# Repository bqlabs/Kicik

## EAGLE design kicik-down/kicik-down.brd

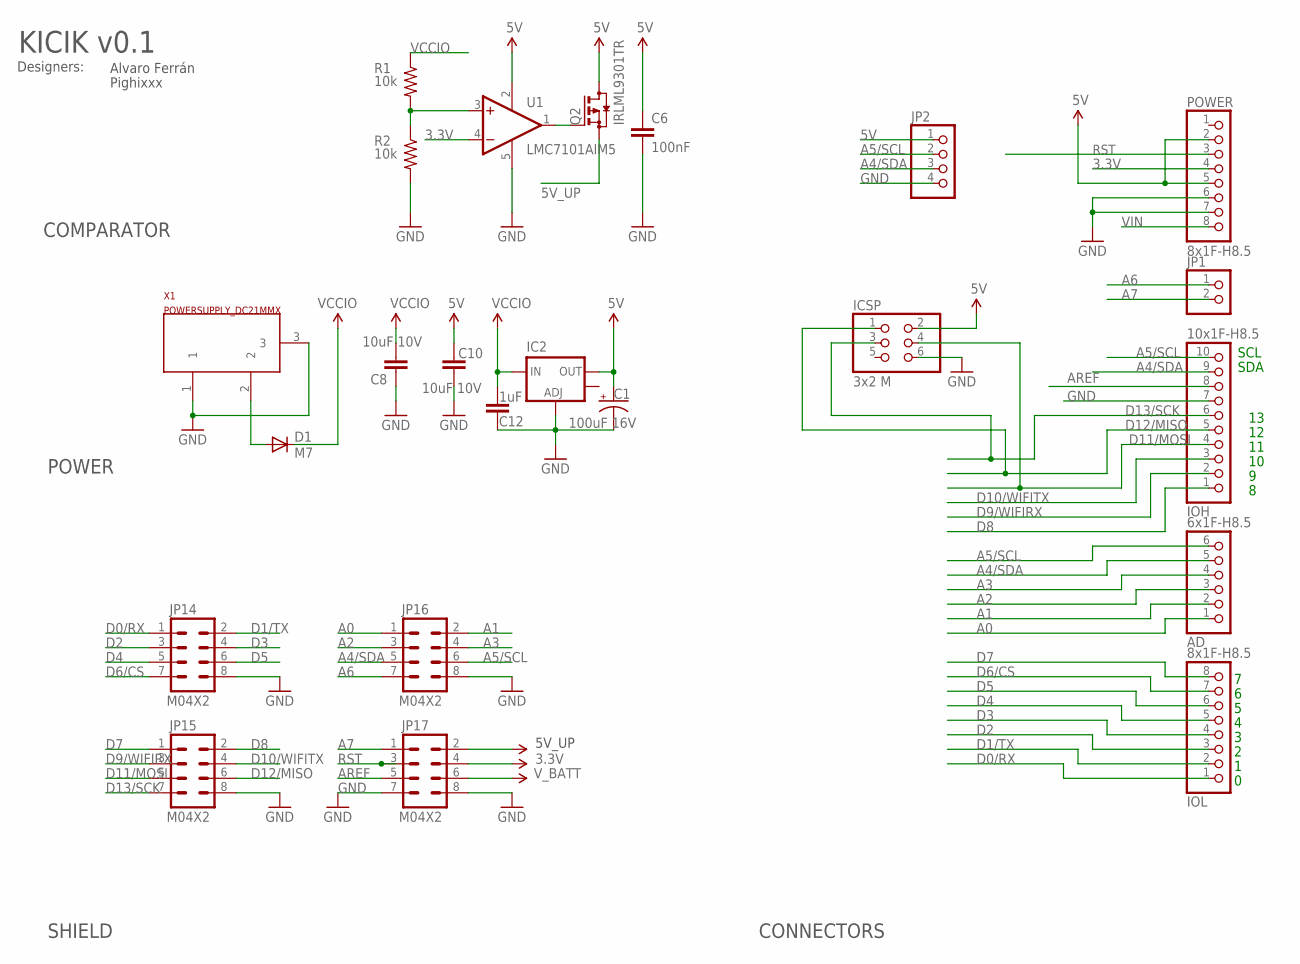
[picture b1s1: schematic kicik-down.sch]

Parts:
AD: 6x1F-H8.5; 1X06
C1: 100uF 16V; PANASONIC_C
C6: 100nF; 0402-CAP
C8, C10: 10uF 10V; 0402-CAP
C12: 1uF; 0402-CAP
D1: M7; SMB
IC2: V_REG_LM1117SOT223; SOT223
ICSP: 3x2 M; 2X03
IOH: 10x1F-H8.5; 1X10
IOL: 8x1F-H8.5; 1X08
JP1: PINHD-1X2; 1X02
JP2: PINHD-1X4; 1X04
JP14, JP15, JP16, JP17: M04X2; 2X4
POWER: 8x1F-H8.5; 1X08
Q2: IRLML9301TR; SOT23
R1, R2: 10k; 0402-RES
U1: LMC7101AIM5; SOT23-5
X1: POWERSUPPLY_DC21MMX; POWERSUPPLY_DC-21MM

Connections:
3.3V: JP17.4, POWER.4, U1.4 (-IN)
5V: C1.+, C6.1, C10.2, IC2.2 (OUT), ICSP.2, JP2.1, POWER.2, POWER.5, Q2.3 (D), U1.2 (V+)
5V_UP: JP17.2, Q2.2 (S)
A0: AD.1, JP16.1
A1: AD.2, JP16.2
A2: AD.3, JP16.3
A3: AD.4, JP16.4
A4/SDA: AD.5, IOH.9, JP2.3, JP16.5
A5/SCL: AD.6, IOH.10, JP2.2, JP16.6
A6: JP1.1, JP16.7
A7: JP1.2, JP17.1
AREF: IOH.8, JP17.5
D0/RX: IOL.1, JP14.1
D1/TX: IOL.2, JP14.2
D2: IOL.3, JP14.3
D3: IOL.4, JP14.4
D4: IOL.5, JP14.5
D5: IOL.6, JP14.6
D6/CS: IOL.7, JP14.7
D7: IOL.8, JP15.1
D8: IOH.1, JP15.2
D9/WIFIRX: IOH.2, JP15.3
D10/WIFITX: IOH.3, JP15.4
D11/MOSI: ICSP.4, IOH.4, JP15.5
D12/MISO: ICSP.1, IOH.5, JP15.6
D13/SCK: ICSP.3, IOH.6, JP15.7
GND: C1.-, C6.2, C8.1, C10.1, C12.1, IC2.1 (ADJ), ICSP.6, IOH.7, JP2.4, JP14.8, JP15.8, JP16.8, JP17.7, JP17.8, POWER.6, POWER.7, R2.2, U1.5 (V-), X1.1, X1.3
unnamed: D1.A, X1.2
unnamed: Q2.1 (G), U1.1 (OUT)
unnamed: R1.2, R2.1, U1.3 (+IN)
RST: JP17.3, POWER.3
VCCIO: C8.2, C12.2, D1.C, IC2.3 (IN), R1.1
VIN: POWER.8
V_BATT: JP17.6

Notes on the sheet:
SDA
SCL
KICIK v0.1
Designers:
Alvaro Ferrán
Pighixxx
POWER
SHIELD
CONNECTORS
COMPARATOR
5V_UP

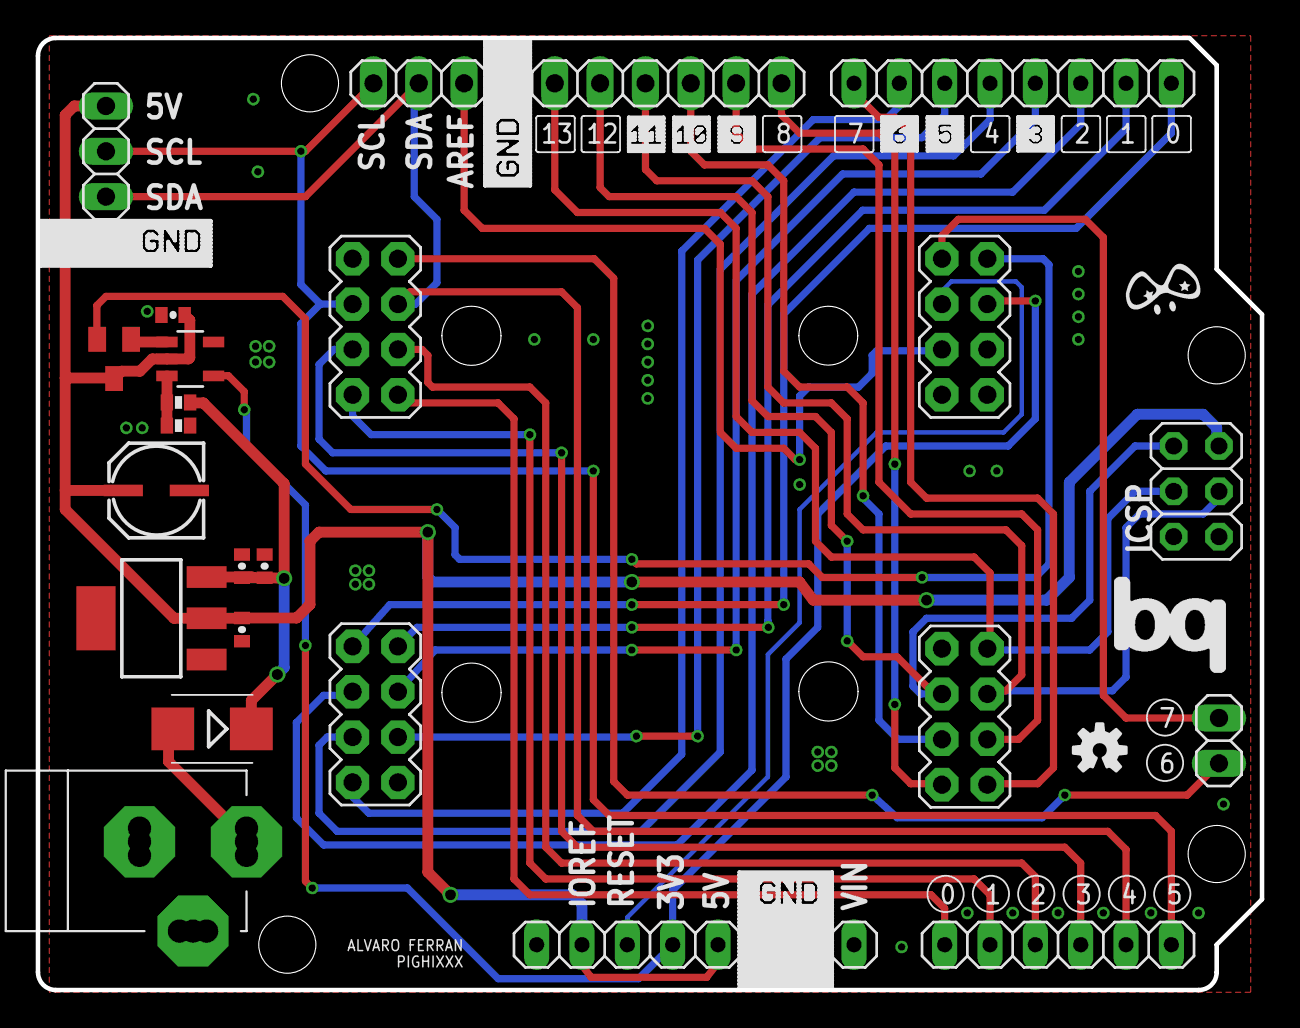
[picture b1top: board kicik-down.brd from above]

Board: 2 copper layers, 68.6 x 53.3 mm, 52 parts (1 on the bottom side), 32 nets.

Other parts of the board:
LOGO3: OSHW-LOGOS; OSHW-LOGO-S
U$1: BQ_LOGO
U$2: PIGHIXXX_LOGO
U$3: S_KICIK_GND_1
U$4: S_KICIK_GND_2
U$5: S_0_P
U$6: S_1_P
U$7: S_2_P
U$8: S_3
U$9: S_4_P
U$10: S_5
U$11: S_6
U$12: S_7_P
U$13: S_8_P
U$14: S_9
U$15: S_10
U$16: S_11
U$17: S_12_P
U$18: S_13_P
U$19: S_0_R_P
U$20: S_1_R_P
U$21: S_2_R_P
U$22: S_3_R_P
U$23: S_4_R_P
U$24: S_5_R_P
U$25: S_6_R_P
U$26: S_7_R_P
U$27: S_KICIK_GND_3
U$28: S_LEGEND

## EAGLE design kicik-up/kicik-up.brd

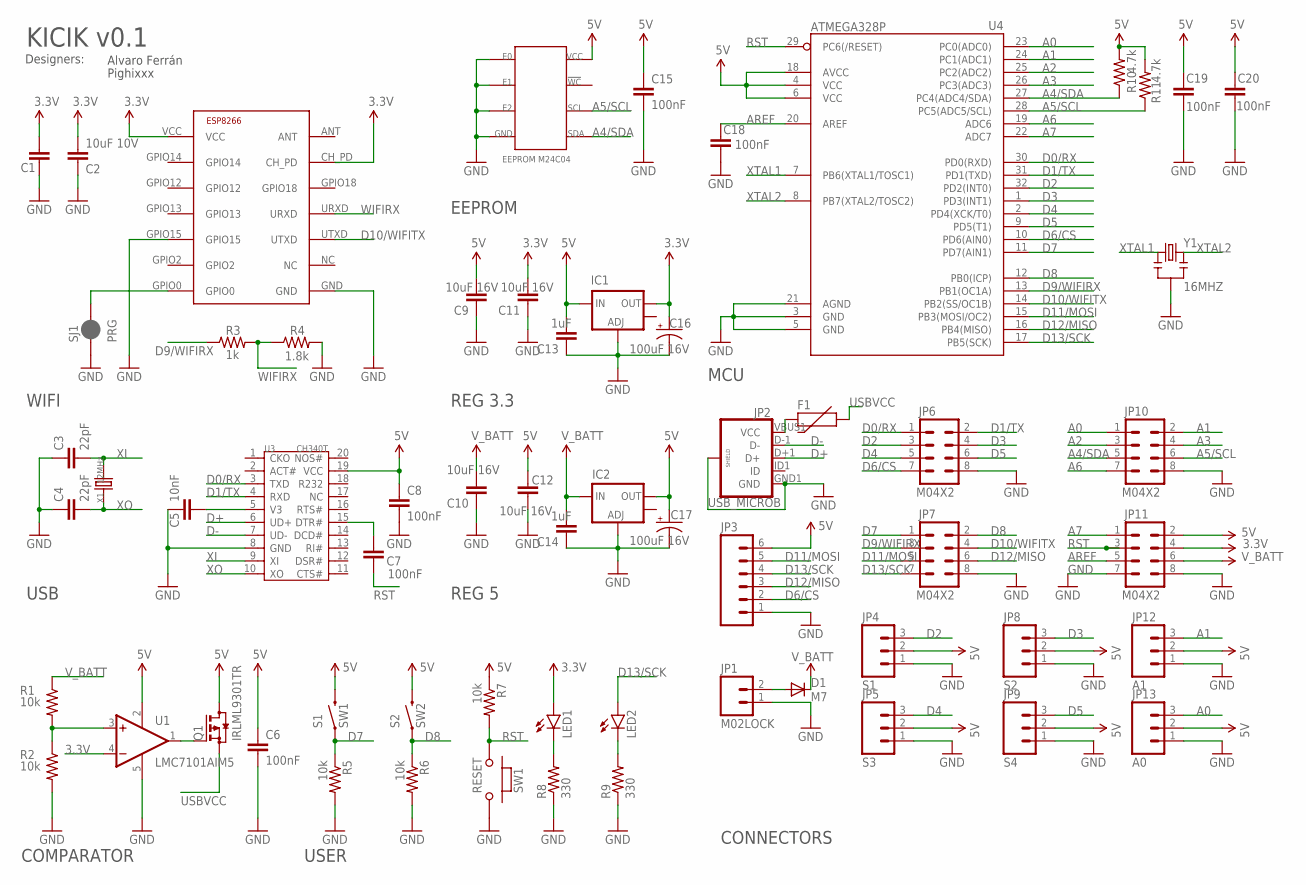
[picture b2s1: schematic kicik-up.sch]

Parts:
C1: 0.1uF; 0402-CAP
C2: 10uF 10V; 0402-CAP
C3, C4: 22pF; 0402-CAP
C5: 10nF; 0402-CAP
C6, C7, C8, C15, C18, C19, C20: 100nF; 0402-CAP
C9, C10, C11, C12: 10uF 16V; 0402-CAP
C13, C14: 1uF; 0402-CAP
C16, C17: 100uF 16V; PANASONIC_C
D1: M7; SMB
F1: PTC0603; 0603
IC1, IC2: V_REG_LM1117SOT223; SOT223
JP1: M02LOCK; 1X02_LOCK
JP2: USB_MICROB; USB-B-MICRO-SMD_V03
JP3: M06LOCK; 1X06_LOCK
JP4: S1; 1X03_LOCK
JP5: S3; 1X03_LOCK
JP6, JP7, JP10, JP11: M04X2; 2X4
JP8: S2; 1X03_LOCK
JP9: S4; 1X03_LOCK
JP12: A1; 1X03_LOCK
JP13: A0; 1X03_LOCK
LED1, LED2: LED0603; LED-0603
M1: M24C04; SO08
Q1: IRLML9301TR; SOT23
R1, R2, R5, R6, R7: 10k; 0402-RES
R3: 1k; 0402-RES
R4: 1.8k; 0402-RES
R8, R9: 330; 0402-RES
R10, R11: 4.7k; 0402-RES
S1: SW1; TACTILE-PTH-SIDEEZ
S2: SW2; TACTILE-PTH-SIDEEZ
SJ1: PRG; PAD-JUMPER-2-NC_BY_PASTE_YES_SILK
SW1: RESET; 157SW
U1: LMC7101AIM5; SOT23-5
U2: ESP8266; ESP-03
U3: CH340T; SSOP20
U4: ATMEGA328P; TQFP32-08
X1: 12MHz; 2P-SMD-5X3.2
Y1: 16MHZ; RESONATOR-SMD

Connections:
3.3V: C1.2, C2.2, C11.2, C16.+, IC1.2 (OUT), JP11.4, LED1.A, U1.4 (-IN), U2.CH_PD, U2.VCC
5V: C6.1, C8.1, C9.2, C12.2, C13.2, C15.1, C17.+, C19.1, C20.1, IC1.3 (IN), IC2.2 (OUT), JP3.6, JP4.2, JP5.2, JP8.2, JP9.2, JP11.2, JP12.2, JP13.2, M1.8 (VCC), Q1.3 (D), R7.1, R10.2, R11.2, S1.2, S2.2, U1.2 (V+), U3.19 (VCC), U4.4 (VCC), U4.6 (VCC), U4.18 (AVCC)
A0: JP10.1, JP13.3, U4.23 (PC0(ADC0))
A1: JP10.2, JP12.3, U4.24 (PC1(ADC1))
A2: JP10.3, U4.25 (PC2(ADC2))
A3: JP10.4, U4.26 (PC3(ADC3))
A4/SDA: JP10.5, M1.5 (SDA), R10.1, U4.27 (PC4(ADC4/SDA))
A5/SCL: JP10.6, M1.6 (SCL), R11.1, U4.28 (PC5(ADC5/SCL))
A6: JP10.7, U4.19 (ADC6)
A7: JP11.1, U4.22 (ADC7)
AREF: C18.1, JP11.5, U4.20 (AREF)
D0/RX: JP6.1, U3.3 (TXD), U4.30 (PD0(RXD))
D1/TX: JP6.2, U3.4 (RXD), U4.31 (PD1(TXD))
D2: JP4.3, JP6.3, U4.32 (PD2(INT0))
D3: JP6.4, JP8.3, U4.1 (PD3(INT1))
D4: JP5.3, JP6.5, U4.2 (PD4(XCK/T0))
D5: JP6.6, JP9.3, U4.9 (PD5(T1))
D6/CS: JP3.2, JP6.7, U4.10 (PD6(AIN0))
D7: JP7.1, R5.1, S1.1, U4.11 (PD7(AIN1))
D8: JP7.2, R6.1, S2.1, U4.12 (PB0(ICP))
D9/WIFIRX: JP7.3, R3.1, U4.13 (PB1(OC1A))
D10/WIFITX: JP7.4, U2.UTXD, U4.14 (PB2(SS/OC1B))
D11/MOSI: JP3.5, JP7.5, U4.15 (PB3(MOSI/OC2))
D12/MISO: JP3.3, JP7.6, U4.16 (PB4(MISO))
D13/SCK: JP3.4, JP7.7, LED2.A, U4.17 (PB5(SCK))
D+: JP2.D+1 (D+), U3.6 (UD+)
D-: JP2.D-1 (D-), U3.7 (UD-)
GND: C1.1, C2.1, C3.1, C4.1, C5.1, C6.2, C8.2, C9.1, C10.1, C11.1, C12.1, C13.1, C14.1, C15.2, C16.-, C17.-, C18.2, C19.2, C20.2, IC1.1 (ADJ), IC2.1 (ADJ), JP1.1, JP2.GND1 (GND), JP2.SHIELD1 (SHIELD), JP2.SHIELD2 (SHIELD), JP2.SHIELD3 (SHIELD), JP3.1, JP4.1, JP5.1, JP6.8, JP7.8, JP8.1, JP9.1, JP10.8, JP11.7, JP11.8, JP12.1, JP13.1, M1.1 (E0), M1.2 (E1), M1.3 (E2), M1.4 (GND), R2.2, R4.2, R5.2, R6.2, R8.1, R9.1, SJ1.1, SW1.2, U1.5 (V-), U2.GND, U2.GPIO15, U3.8 (GND), U4.3 (GND), U4.5 (GND), U4.21 (AGND), Y1.2
unnamed: C7.1, U3.15 (DTR#)
unnamed: LED1.C, R8.2
unnamed: F1.2, JP2.VBUS1 (VCC)
unnamed: R1.2, R2.1, U1.3 (+IN)
unnamed: SJ1.2, U2.GPIO0
unnamed: D1.A, JP1.2
unnamed: LED2.C, R9.2
unnamed: Q1.1 (G), U1.1 (OUT)
RST: C7.2, JP11.3, R7.2, SW1.1, U4.29 (PC6(/RESET))
USBVCC: F1.1, Q1.2 (S)
V3: C5.2, U3.5 (V3)
V_BATT: C10.2, C14.2, D1.C, IC2.3 (IN), JP11.6, R1.1
WIFIRX: R3.2, R4.1, U2.URXD
XI: C3.2, U3.9 (XI), X1.2
XO: C4.2, U3.10 (XO), X1.1
XTAL1: U4.7 (PB6(XTAL1/TOSC1)), Y1.1
XTAL2: U4.8 (PB7(XTAL2/TOSC2)), Y1.3

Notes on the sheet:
KICIK v0.1
Designers:
Alvaro Ferrán
Pighixxx
USER
WIFI
EEPROM
REG 3.3
REG 5
CONNECTORS
USB
MCU
COMPARATOR

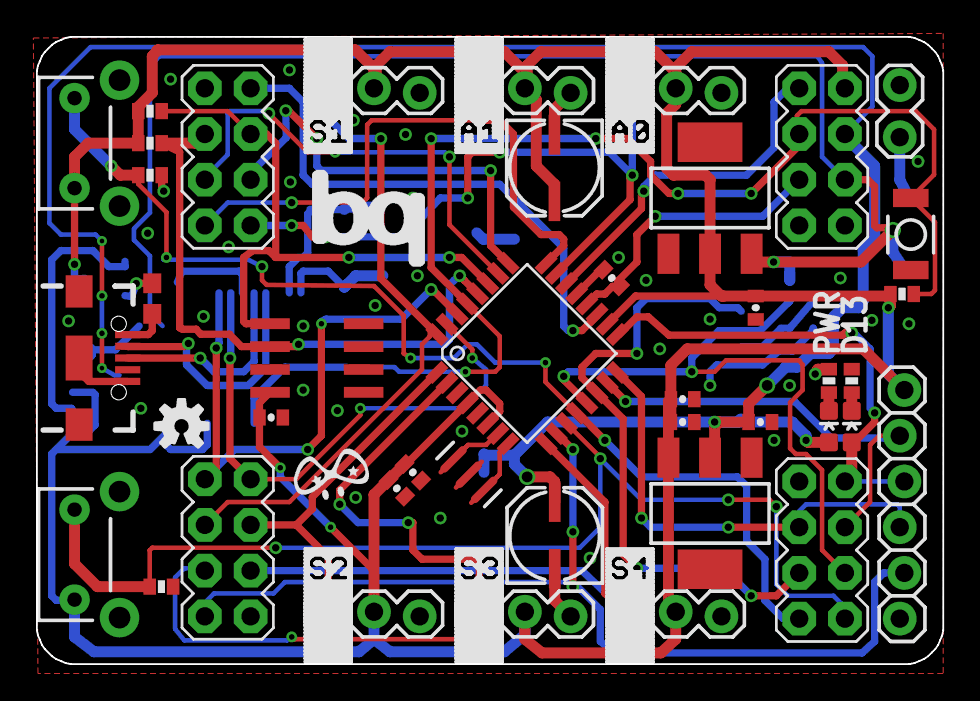
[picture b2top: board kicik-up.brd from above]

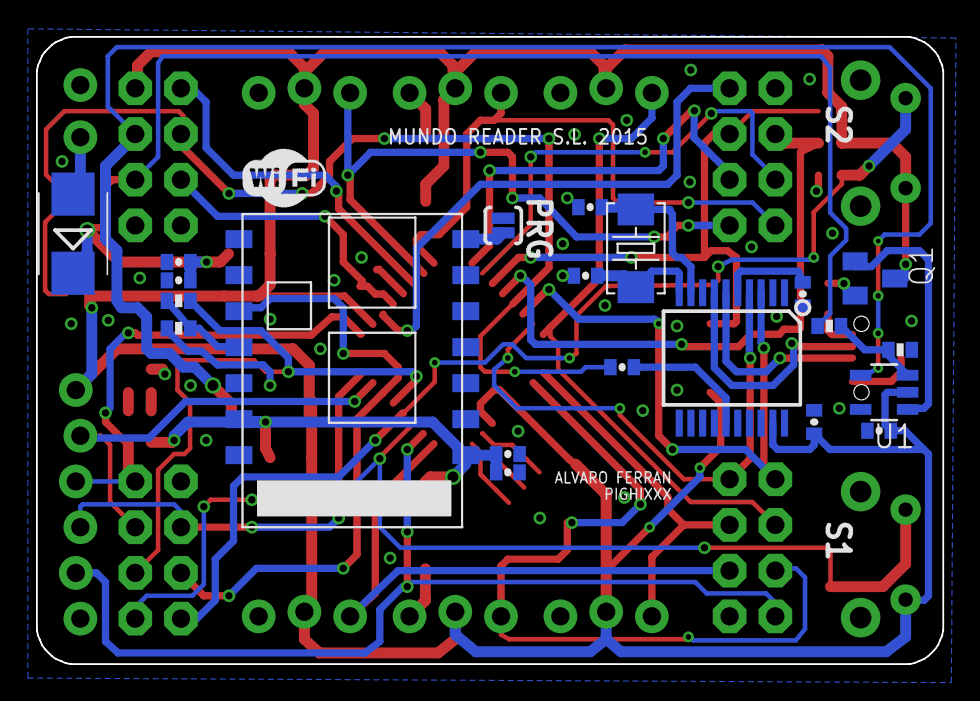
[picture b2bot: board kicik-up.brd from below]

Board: 2 copper layers, 50.4 x 34.8 mm, 72 parts (22 on the bottom side), 45 nets.

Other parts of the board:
LOGO3: OSHW-LOGOS; OSHW-LOGO-S
U$1: S_WIFI
U$2: PIGHIXXX_LOGO
U$3: BQ_LOGO
U$4: S_S1
U$5: S_A1
U$6: S_A0
U$7: S_S2
U$8: S_S3
U$9: S_S4

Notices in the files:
parts and their libraries:
SparkFun-Connectors: Licensing: Creative Commons ShareAlike 4.0 International - https://creativecommons.org/licenses/by-sa/4.0
